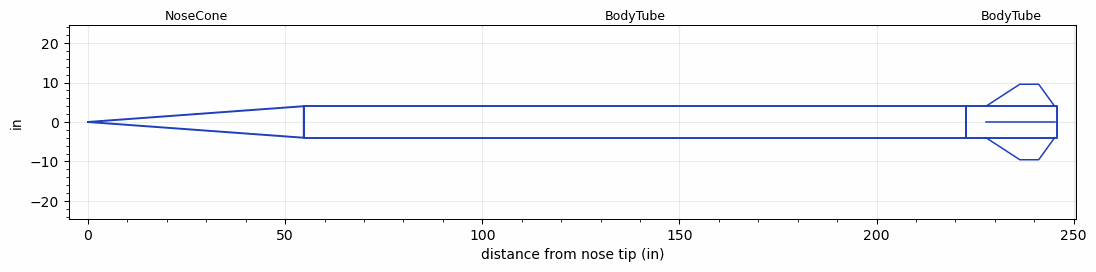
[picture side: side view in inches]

<RASAeroDocument>
 <FileVersion>2</FileVersion>
 <RocketDesign>
  <NoseCone>
   <Length>54.7243</Length>
   <Diameter>8</Diameter>
   <Shape>Conical</Shape>
   <Location>0</Location>
  </NoseCone>
  <BodyTube>
   <Length>167.9997</Length>
   <Diameter>8</Diameter>
   <Location>54.7243</Location>
  </BodyTube>
  <BodyTube>
   <Length>23</Length>
   <Diameter>8</Diameter>
   <Location>222.724</Location>
   <Fin>
    <Count>4</Count>
    <Chord>17.3948</Chord>
    <Span>5.5725</Span>
    <SweepDistance>8.5677</SweepDistance>
    <TipChord>4.7905</TipChord>
    <Thickness>0.25</Thickness>
    <Location>17.946</Location>
    <AirfoilSection>Square</AirfoilSection>
   </Fin>
  </BodyTube>
  <Surface>Rough Camouflage Paint</Surface>
  <CD>0</CD>
  <ModifiedBarrowman>False</ModifiedBarrowman>
  <Turbulence>False</Turbulence>
  <UseBooster1>False</UseBooster1>
  <UseBooster2>False</UseBooster2>
  <Comments>Testing for stability --&gt; upthrust sim</Comments>
 </RocketDesign>
 <LaunchSite>
  <Altitude>0</Altitude>
  <Pressure>29.9214</Pressure>
  <RodAngle>0</RodAngle>
  <RodLength>3.2808</RodLength>
  <Temperature>59</Temperature>
  <WindSpeed>4.4739</WindSpeed>
 </LaunchSite>
 <Recovery>
  <Altitude1>0</Altitude1>
  <Altitude2>0</Altitude2>
  <DeviceType1>None</DeviceType1>
  <DeviceType2>None</DeviceType2>
  <Event1>False</Event1>
  <Event2>False</Event2>
  <Size1>0</Size1>
  <Size2>0</Size2>
  <EventType1>None</EventType1>
  <EventType2>None</EventType2>
  <CD1>0</CD1>
  <CD2>0</CD2>
 </Recovery>
 <SimulationList>
  <Simulation>
   <SustainerLaunchWt>119.0109</SustainerLaunchWt>
   <SustainerCG>149.7334</SustainerCG>
   <SustainerIgnitionDelay>0</SustainerIgnitionDelay>
   <Booster1SeparationDelay>0</Booster1SeparationDelay>
   <Booster1IgnitionDelay>0</Booster1IgnitionDelay>
   <IncludeBooster1>False</IncludeBooster1>
   <Booster2Delay>0</Booster2Delay>
   <IncludeBooster2>False</IncludeBooster2>
  </Simulation>
 </SimulationList>
</RASAeroDocument>
